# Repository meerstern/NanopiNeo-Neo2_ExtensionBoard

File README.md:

# NanopiNeo-Neo2_ExtensionBoard
The extension board of Kicad Files for Nano Pi Neo/Neo2 with USB and RTC, grove con.

[FriendlyElec製NanoPi Neo/Neo2][0]の拡張ボードです。<br>
ピンヘッダ上にあるUSB2ポート、I2Cポート(Grove)のコネクタを搭載しています。<br>
標準USBの1ポートで足りないという場合やGroveで拡張したいという場合に最適です。<br>
また、I2Cポートには[純正NASキット][1]と同じ[RTC　DS1307][2]が搭載しています。<br>
そのため、電源断でも時刻を保持することが可能です。<br>

## NanoPi Neo/Neo2拡張ボード仕様
  * USB2ポート(フルサイズtypeA、USB1、USB2)搭載
  * I2Cポート(Groveコネクタ、I2C0)搭載
  * RTC(リアルタイムクロック、DS1307、CR1220 or CR1225バッテリ、I2C0内部接続)搭載
  * I2Cは10kでプルアップ抵抗を基板回路に搭載
  
## NanoPi Neo/Neo2 RTC設定/読み込み方法
  1. RTC接続の有無確認    
  ```sudo i2cdetect -y 0```    
  68が表示されていれば、RTCが正常に接続されています。
  
  1. Neo/Neo2時刻設定  
  ```sudo date +%T -s "19:52:00"```  
  ```sudo date +%Y%m%d -s "20180518"```  

  1. RTC DS1307ドライバ読み込み<br>
  ```echo ds1307 0x68 > /sys/class/i2c-adapter/i2c-0/new_device```<br>
  ```sudo modprobe rtc-ds1307```
  
  1. 時刻のRTCへの書き込み<br> 
  ```sudo hwclock -w -f /dev/rtc*```  
  *は1、2...といった数字が入ります。機器によって異なります。  
  
  1. 起動時の時刻のRTCからの読み込み<br>
  ```sudo hwclock -s -f /dev/rtc*```  
  *は1、2...といった数字が入ります。機器によって異なります。 
  
## NanoPi Neo/Neo2拡張ボード使用例

　ピンヘッダは別売、別途はんだ付けが必要です。

## NanoPi Neo/Neo2拡張ボード注意点
  * NanoPi Neo/Neo2のGPIO1、GPIO2に接続するためのピンヘッダは別売りです。
  * 取付するピンヘッダの長さが標準的な10mmの場合、電源供給用microUSBと拡張ボードのUSBが干渉してどちらかが使用できません。<br>
 この場合は長いピンヘッダやピンコネクタを使用して干渉を回避するか、
 microUSBを使用せずにDebugUARTピンをヒートシンク横から取り出して5V電源を供給してください。
  * RTCは静電気等による破損防止のため、必ず電池を入れて使用してください。

[0]: http://www.friendlyarm.com/index.php?route=product/product&product_id=180 "*0"
[1]: http://www.friendlyarm.com/index.php?route=product/product&product_id=192 "*1"
[2]: https://www.maximintegrated.com/en/products/digital/real-time-clocks/DS1307.html "*1"

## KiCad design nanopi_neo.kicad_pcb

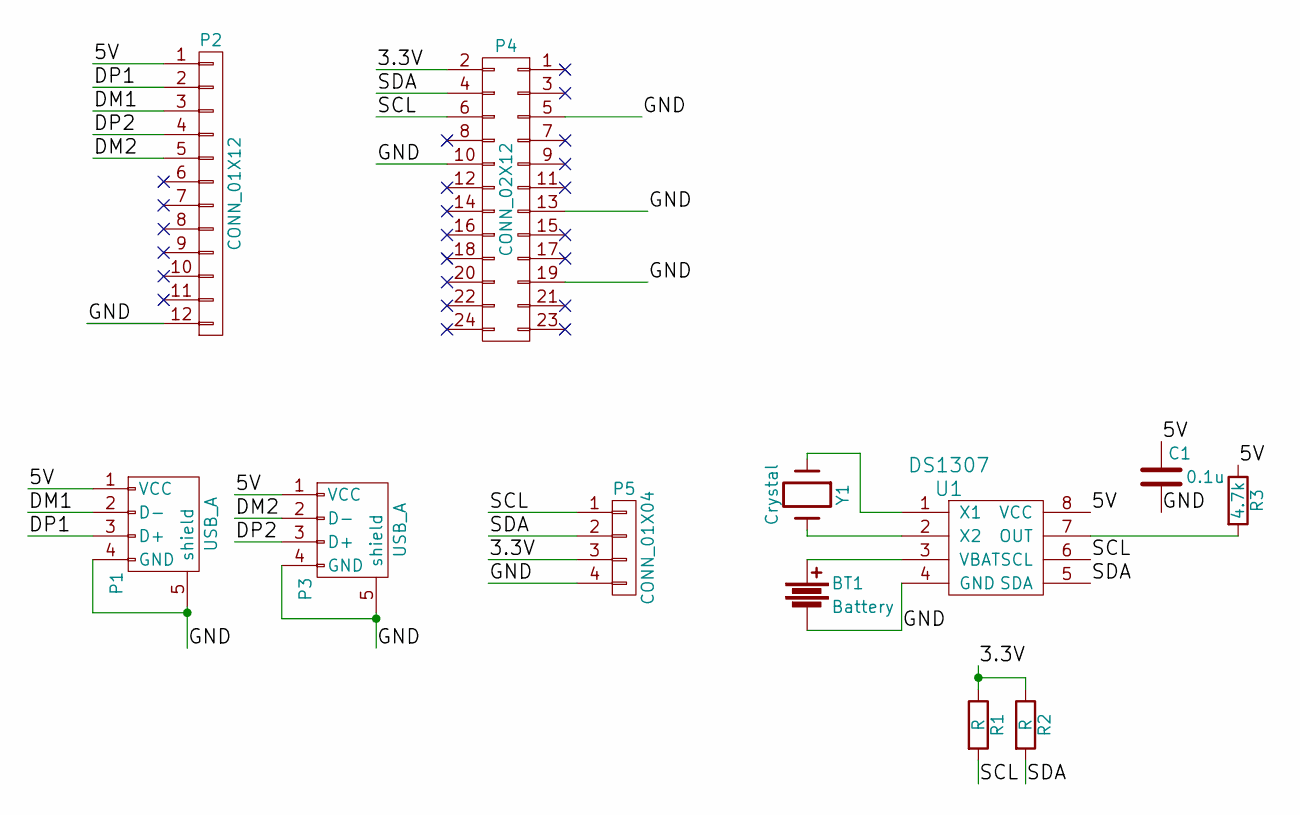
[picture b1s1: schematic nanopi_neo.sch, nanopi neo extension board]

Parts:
BT1: Battery; CR1220
C1: 0.1u; C-0603
P1, P3: USB_A; USBHOST
P2: CONN_01X12; pinhead-1X12
P4: CONN_02X12; pinhead-2X12
P5: CONN_01X04; GROVE
R1, R2: R; R-0603
R3: 4.7k; R-0603
U1: DS1307; 8
Y1: Crystal; ECS-31B_xtal

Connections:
/3.3V: P4.2, P5.3, R1.1, R2.1
/5V: C1.1, P1.1 (VCC), P2.1, P3.1 (VCC), R3.1, U1.8 (VCC)
/DM1: P1.2 (D-), P2.3
/DM2: P2.5, P3.2 (D-)
/DP1: P1.3 (D+), P2.2
/DP2: P2.4, P3.3 (D+)
/GND: BT1.2, C1.2, P1.4 (GND), P1.5 (shield), P2.12, P3.4 (GND), P3.5 (shield), P4.5, P4.10, P4.13, P4.19, P5.4, U1.4 (GND)
/SCL: P4.6, P5.1, R1.2, U1.6 (SCL)
/SDA: P4.4, P5.2, R2.2, U1.5 (SDA)
unnamed: BT1.1, U1.3 (VBAT)
unnamed: R3.2, U1.7 (OUT)
unnamed: U1.1 (X1), Y1.1
unnamed: U1.2 (X2), Y1.2

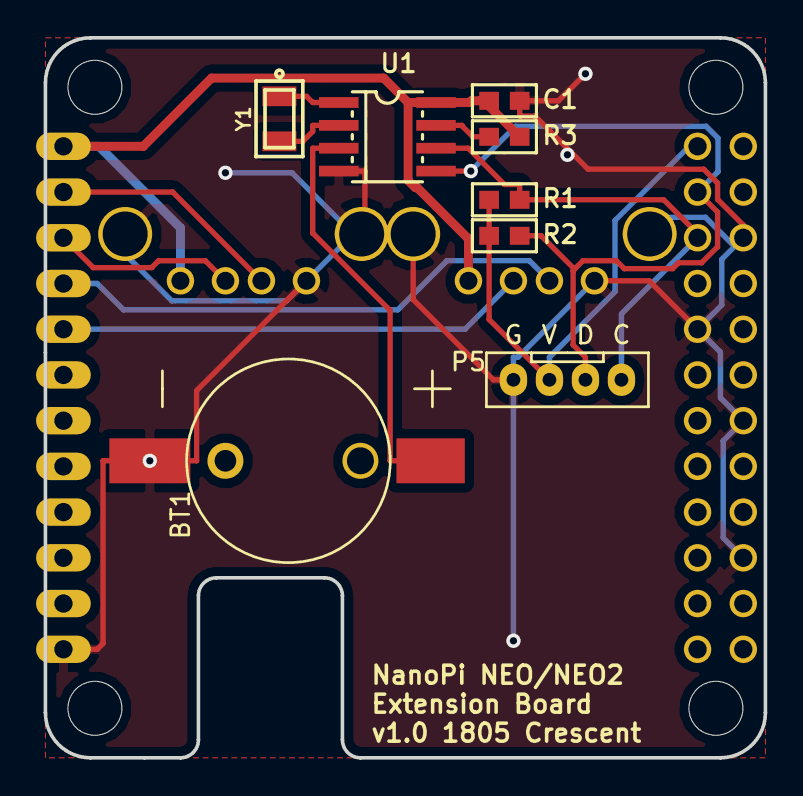
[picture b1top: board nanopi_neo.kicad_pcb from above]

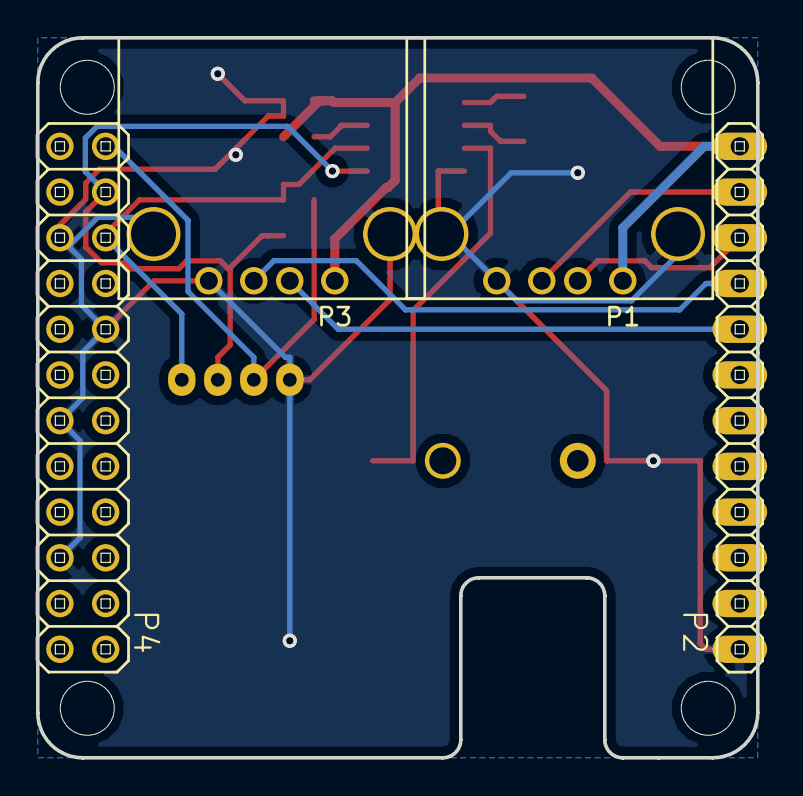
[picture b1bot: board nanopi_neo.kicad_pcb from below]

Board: 2 copper layers, 40.0 x 40.0 mm, 16 parts (4 on the bottom side), 13 nets.

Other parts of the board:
REF1, REF2, REF3, REF4: MountingHole_3mm

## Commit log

2018-05-19 Init
2018-05-20 Add image
